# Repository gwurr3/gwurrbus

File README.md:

# gwurrbus

gwurrbus is a starting point for making a network of RS-485 connected atmel AVR devices.

  - Controlled by a *BSD box via the serial port and an RS-232 to RS-485 adapter
  - Currently only for the atmega328p but more ports coming soon
  - BSD/ISC Licensed

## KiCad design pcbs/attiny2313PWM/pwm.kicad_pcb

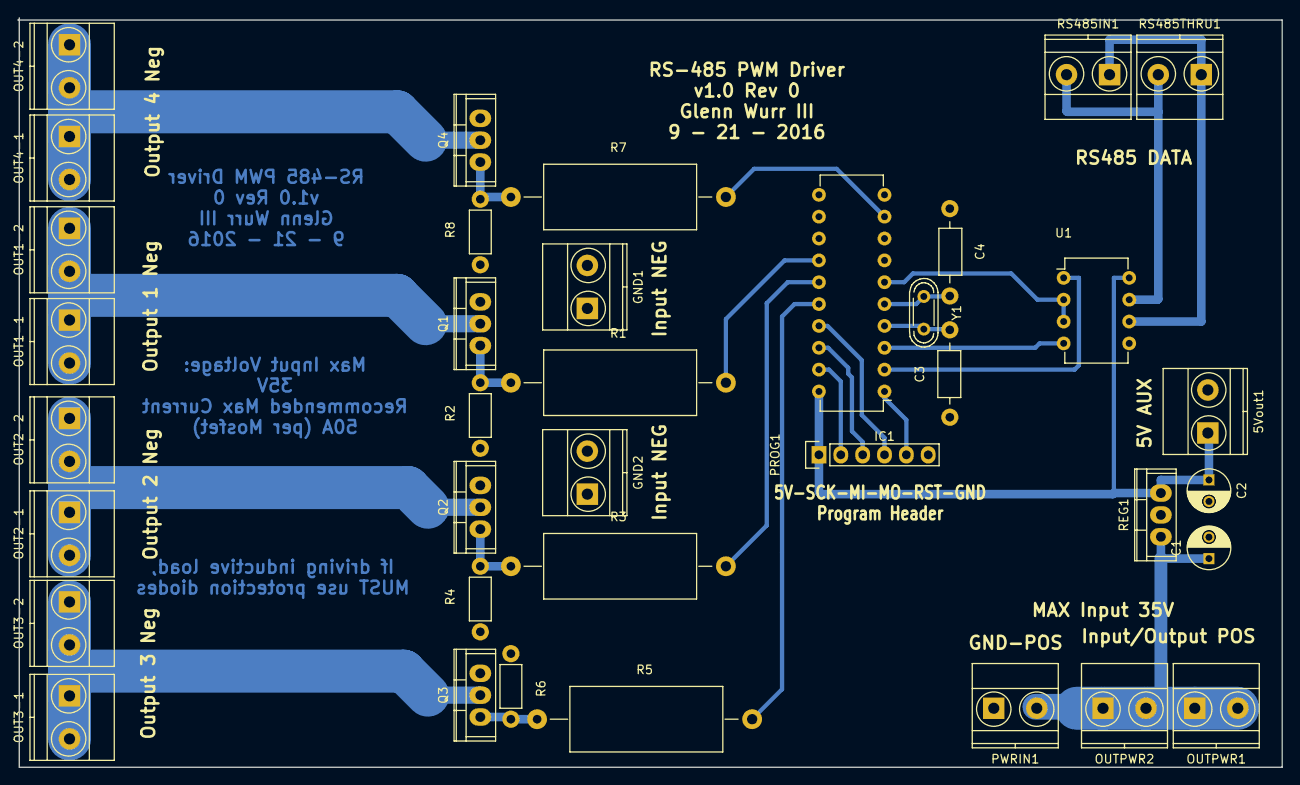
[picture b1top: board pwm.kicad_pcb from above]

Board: 2 copper layers, 147.0 x 87.1 mm, 37 parts (0 on the bottom side), 26 nets.

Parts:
5Vout1: CONN_01X02; TerminalBlock_Pheonix_MKDS1.5-2pol
C1: 1uf; C_Radial_D5_L6_P2.5
C2: 10uf; C_Radial_D5_L6_P2.5
C3, C4: C_Small; Choke_Horizontal_RM10mm
GND1, GND2: CONN_01X02; TerminalBlock_Pheonix_MKDS1.5-2pol
IC1: ATTINY2313A-P; DIP-20_W7.62mm
OUT1-1, OUT1-2, OUT2-1, OUT2-2, OUT3-1, OUT3-2, OUT4-1, OUT4-2: CONN_01X02; TerminalBlock_Pheonix_MKDS1.5-2pol
OUTPWR1, OUTPWR2: CONN_01X02; TerminalBlock_Pheonix_MKDS1.5-2pol
PROG1: CONN_01X06; Pin_Header_Straight_1x06
PWRIN1: CONN_01X02; TerminalBlock_Pheonix_MKDS1.5-2pol
Q1, Q2, Q3, Q4: IRF540N; TO-220
R1, R3, R5, R7: 68R; Resistor_Horizontal_RM25mm
R2, R4, R6, R8: 2.2k; Resistor_Horizontal_RM7mm
REG1: LM7805CT; TO-220
RS485IN1, RS485THRU1: CONN_01X02; TerminalBlock_Pheonix_MKDS1.5-2pol
U1: SP3485CP; DIP-8_W7.62mm
Y1: Crystal; Crystal_HC52-U_Vertical

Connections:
+5V: 5Vout1.1, C2.1, IC1.20, PROG1.1, REG1.3, U1.8
/MISO: IC1.18, PROG1.3
/MOSI: IC1.17, PROG1.4
/OUT1: OUT1-1.1, OUT1-1.2, OUT1-2.1, OUT1-2.2, Q1.2
/OUT2: OUT2-1.1, OUT2-1.2, OUT2-2.1, OUT2-2.2, Q2.2
/OUT3: OUT3-1.1, OUT3-1.2, OUT3-2.1, OUT3-2.2, Q3.2
/OUT4: OUT4-1.1, OUT4-1.2, OUT4-2.1, OUT4-2.2, Q4.2
/PWM1: IC1.14, R1.2
/PWM2: IC1.15, R3.2
/PWM3: IC1.16, R5.2
/PWM4: IC1.9, R7.2
/RESET: IC1.1, PROG1.5
/RS485A: RS485IN1.1, RS485THRU1.1, U1.6
/RS485B: RS485IN1.2, RS485THRU1.2, U1.7
/SCK: IC1.19, PROG1.2
Earth: 5Vout1.2, C1.2, C2.2, C3.1, C4.1, GND1.1, GND1.2, GND2.1, GND2.2, IC1.10, PROG1.6, PWRIN1.1, Q1.3, Q2.3, Q3.3, Q4.3, R2.1, R4.1, R6.1, R8.1, REG1.2, U1.5
unnamed: C3.2, IC1.4, Y1.2
unnamed: C4.2, IC1.5, Y1.1
unnamed: IC1.2, U1.1
unnamed: IC1.3, U1.4
unnamed: IC1.6, U1.2, U1.3
unnamed: Q1.1, R1.1, R2.2
unnamed: Q2.1, R3.1, R4.2
unnamed: Q3.1, R5.1, R6.2
unnamed: Q4.1, R7.1, R8.2
VCC: C1.1, OUTPWR1.1, OUTPWR1.2, OUTPWR2.1, OUTPWR2.2, PWRIN1.2, REG1.1

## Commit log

2016-09-21 added some PCBs
2016-09-21 fixed footprint on crystal
2016-09-21 cleanup ps file
2016-10-04 make portable to attiny2313
2016-10-04 porting efforts to attiny2313
2016-10-04 porting efforts to attiny2313 again
2016-10-04 cleaner
2016-10-06 getting somewhere with the attiny. was running out of RAM. DUH!
